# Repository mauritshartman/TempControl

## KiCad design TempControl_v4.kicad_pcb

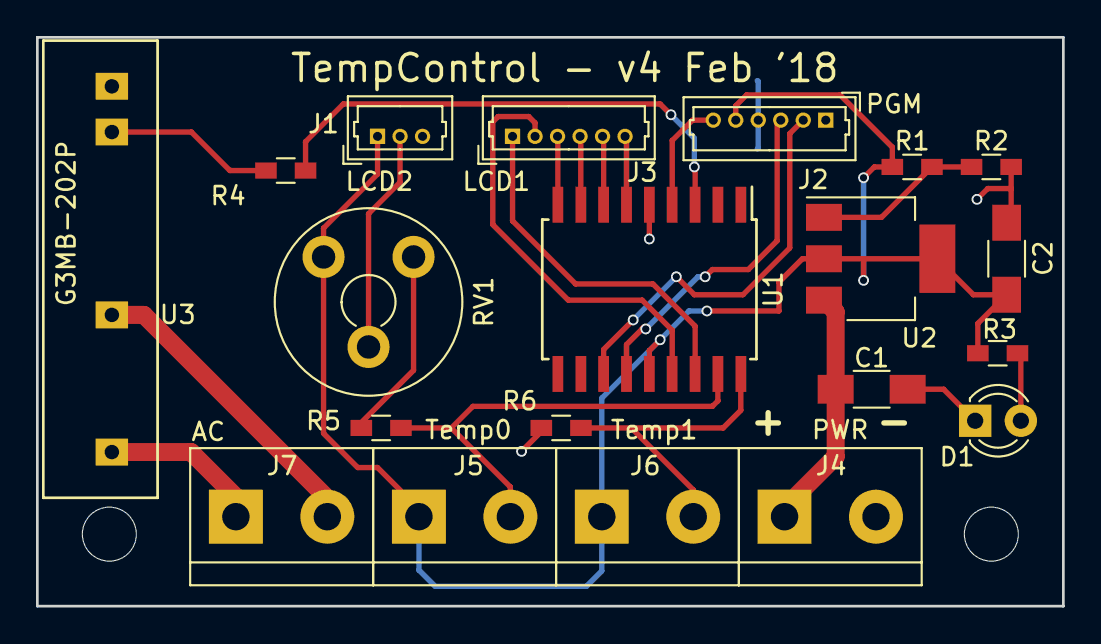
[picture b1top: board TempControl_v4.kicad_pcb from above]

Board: 2 copper layers, 57.0 x 31.6 mm, 20 parts (0 on the bottom side), 21 nets.

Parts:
C1: 1uF; C_1206_HandSoldering
C2: 10uF; C_1206_HandSoldering
D1: LED; LED_D3.0mm
J1: LCD2; Molex_PicoBlade_53047-0310_03x1.25mm_Straight
J2: PGM; Molex_PicoBlade_53047-0610_06x1.25mm_Straight
J3: LCD1; Molex_PicoBlade_53047-0610_06x1.25mm_Straight
J4: PWR; TerminalBlock_bornier-2_P5.08mm
J5: Temp0; TerminalBlock_bornier-2_P5.08mm
J6: Temp1; TerminalBlock_bornier-2_P5.08mm
J7: AC; TerminalBlock_bornier-2_P5.08mm
R1: 240R; R_0603_HandSoldering
R2: 720R; R_0603_HandSoldering
R3: 1k; R_0603_HandSoldering
R4: 470; R_0603_HandSoldering
R5, R6: 100k; R_0603_HandSoldering
RV1: POT; Potentiometer_Trimmer_Piher_PT-10v5_Horizontal_Px5.0mm_Py5.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
U1: PIC16(L)F88-I/P; SOIC-18W_7.5x11.6mm_Pitch1.27mm
U2: LM317_3PinPackage; SOT-223-3_TabPin2
U3: G3MB-202P

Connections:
+5V: C2.1, J1.1, J2.5, J5.1, J6.1, R1.1, R3.1, RV1.1, U1.14, U2.2
/PIC_PGC: J2.2, U1.12
/PIC_PGD: J2.3, U1.13
/PIC_VPP: J2.6, U1.4
/Power_supply/PWR_pos: C1.1, J4.1, U2.3
/Relais/AC1_out: J7.1, U3.1
/Relais/AC2_out: J7.2, U3.2
/Relais/relais_trig: R4.2, U1.3
/Thermistor0/Thermistor_2: J5.2, R5.1, U1.17
/Thermistor1/Thermistor_2: J6.2, R6.1, U1.18
GND: C1.2, C2.2, D1.1, J1.3, J2.4, J4.2, R2.2, R5.2, R6.2, RV1.3, U1.5, U3.4
unnamed: D1.2, R3.2
unnamed: J1.2, RV1.2
unnamed: J3.1, U1.16
unnamed: J3.2, U1.15
unnamed: J3.3, U1.9
unnamed: J3.4, U1.8
unnamed: J3.5, U1.7
unnamed: J3.6, U1.6
unnamed: R1.2, R2.1, U2.1
unnamed: R4.1, U3.3

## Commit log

2017-11-18 Added PT100 amplifier subcircuit
2017-11-18 Added relais and power supply
2017-11-19 Added footprints to main schematic
2017-11-19 Completed all footprints except SSR
2017-11-19 Added G3MB footprint
2017-11-19 Initial PCB design
2017-11-21 Completed PCB layout
2017-11-21 Added logo to PCB
2018-02-19 Change from PT100 to thermistor
2018-02-19 Moved logo to bottom side
